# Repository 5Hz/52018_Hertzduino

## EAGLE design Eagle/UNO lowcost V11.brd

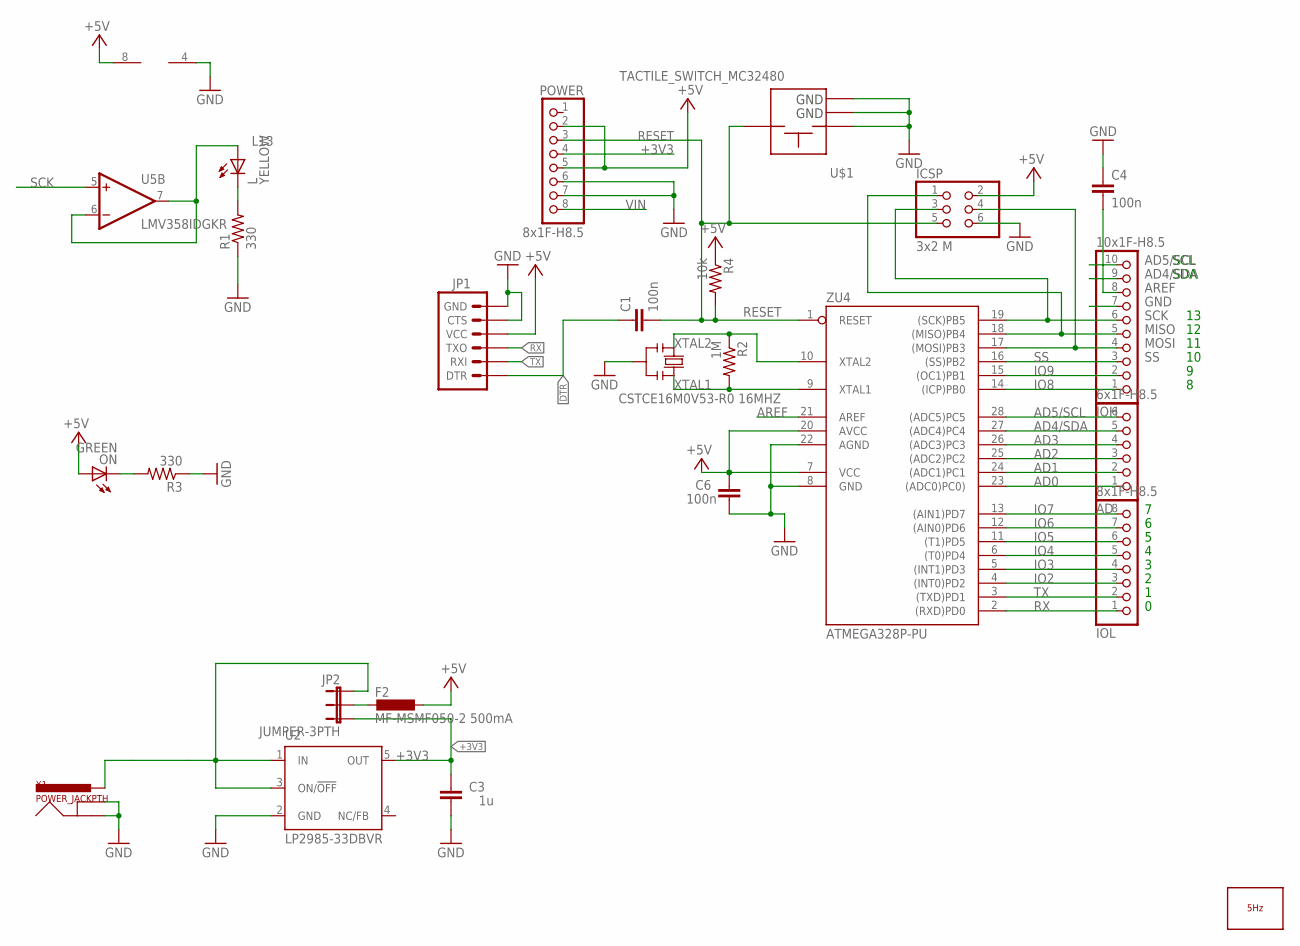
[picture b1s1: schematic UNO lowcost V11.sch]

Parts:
AD: 6x1F-H8.5; 1X06
C1, C4, C6: 100n; C0603-ROUND
C3: 1u; C0603-ROUND
F2: MF-MSMF050-2 500mA; L1812
ICSP: 3x2 M; 2X03
IOH: 10x1F-H8.5; 1X10
IOL: 8x1F-H8.5; 1X08
JP1: ARDUINO_SERIAL_PROGRAMPTH; 1X06
JP2: JUMPER-3PTH; 1X03
L: YELLOW; CHIP-LED0603
LOGO1: LOGO_5HZ_H_20MM; 5HZ_LOGO_H_20MM
ON: GREEN; CHIP-LED0603
POWER: 8x1F-H8.5; 1X08
R1, R3: 330; 0603-RES
R2: 1M; 0603-RES
R4: 10k; 0603-RES
U2: LP2985-33DBVR; SOT23-DBV
U5: LMV358IDGKR; MSOP08
U$1: TACTILE_SWITCH_MC32480; MC32840
X1: POWER_JACKPTH; POWER_JACK_PTH
Y2: CSTCE16M0V53-R0 16MHZ; RESONATOR
ZU4: ATMEGA328P-PU; DIL28-3

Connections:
5V/3V3: F2.2, JP2.2
+3V3: C3.2, JP2.3, POWER.4, U2.5 (OUT)
+5V: C6.2, F2.1, ICSP.2, JP1.4 (VCC), ON.A, POWER.2, POWER.5, R4.1, U5.8 (V+), ZU4.7 (VCC), ZU4.20 (AVCC)
AD0: AD.1, ZU4.23 ((ADC0)PC0))
AD1: AD.2, ZU4.24 ((ADC1)PC1)
AD2: AD.3, ZU4.25 ((ADC2)PC2)
AD3: AD.4, ZU4.26 ((ADC3)PC3)
AD4/SDA: AD.5, IOH.9, ZU4.27 ((ADC4)PC4)
AD5/SCL: AD.6, IOH.10, ZU4.28 ((ADC5)PC5)
AREF: C4.2, IOH.8, ZU4.21 (AREF)
DTR: C1.1, JP1.1 (DTR)
GND: C3.1, C4.1, C6.1, ICSP.6, IOH.7, JP1.5 (CTS), JP1.6 (GND), POWER.6, POWER.7, R1.1, R3.1, U2.2 (GND), U5.4 (V-), U$1.A@1 (A), U$1.GND@1 (GND), U$1.GND@2 (GND), X1.GND, X1.GNDBREAK, Y2.2, ZU4.8 (GND), ZU4.22 (AGND)
IO2: IOL.3, ZU4.4 ((INT0)PD2)
IO3: IOL.4, ZU4.5 ((INT1)PD3)
IO4: IOL.5, ZU4.6 ((T0)PD4)
IO5: IOL.6, ZU4.11 ((T1)PD5)
IO6: IOL.7, ZU4.12 ((AIN0)PD6)
IO7: IOL.8, ZU4.13 ((AIN1)PD7)
IO8: IOH.1, ZU4.14 ((ICP)PB0)
IO9: IOH.2, ZU4.15 ((OC1)PB1)
L13: L.A, U5.6 (-IN), U5.7 (OUT)
MISO: ICSP.1, IOH.5, ZU4.18 ((MISO)PB4)
MOSI: ICSP.4, IOH.4, ZU4.17 ((MOSI)PB3)
unnamed: L.C, R1.2
unnamed: ON.C, R3.2
RESET: C1.2, ICSP.5, POWER.3, R4.2, U$1.B, ZU4.1 (RESET)
RX: IOL.1, JP1.3 (TXO), ZU4.2 ((RXD)PD0)
SCK: ICSP.3, IOH.6, U5.5 (+IN), ZU4.19 ((SCK)PB5)
SS: IOH.3, ZU4.16 ((SS)PB2)
TX: IOL.2, JP1.2 (RXI), ZU4.3 ((TXD)PD1)
VIN: JP2.1, POWER.8, U2.1 (IN), U2.3 (ON/!OFF), X1.PWR
XTAL1: R2.2, Y2.3, ZU4.9 (XTAL1)
XTAL2: R2.1, Y2.1, ZU4.10 (XTAL2)

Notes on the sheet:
SDA
SCL

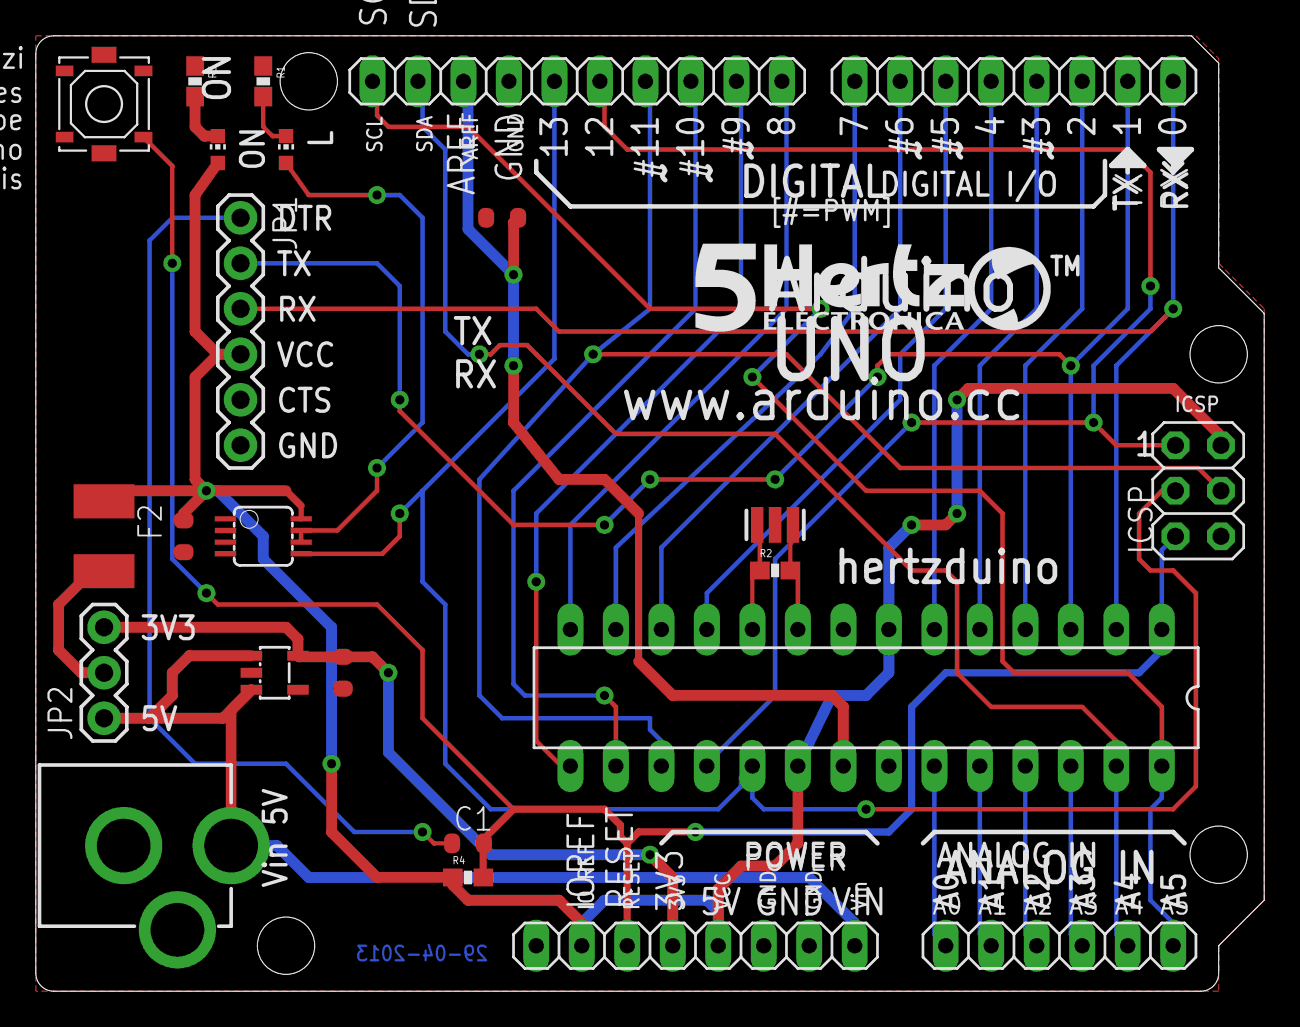
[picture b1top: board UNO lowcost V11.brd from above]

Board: 2 copper layers, 68.6 x 53.3 mm, 25 parts (0 on the bottom side), 33 nets.

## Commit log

2014-01-14 creación

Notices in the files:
parts and their libraries:
SparkFun: Licensing: CC v3.0 Share-Alike You are welcome to use this library for commercial purposes.
